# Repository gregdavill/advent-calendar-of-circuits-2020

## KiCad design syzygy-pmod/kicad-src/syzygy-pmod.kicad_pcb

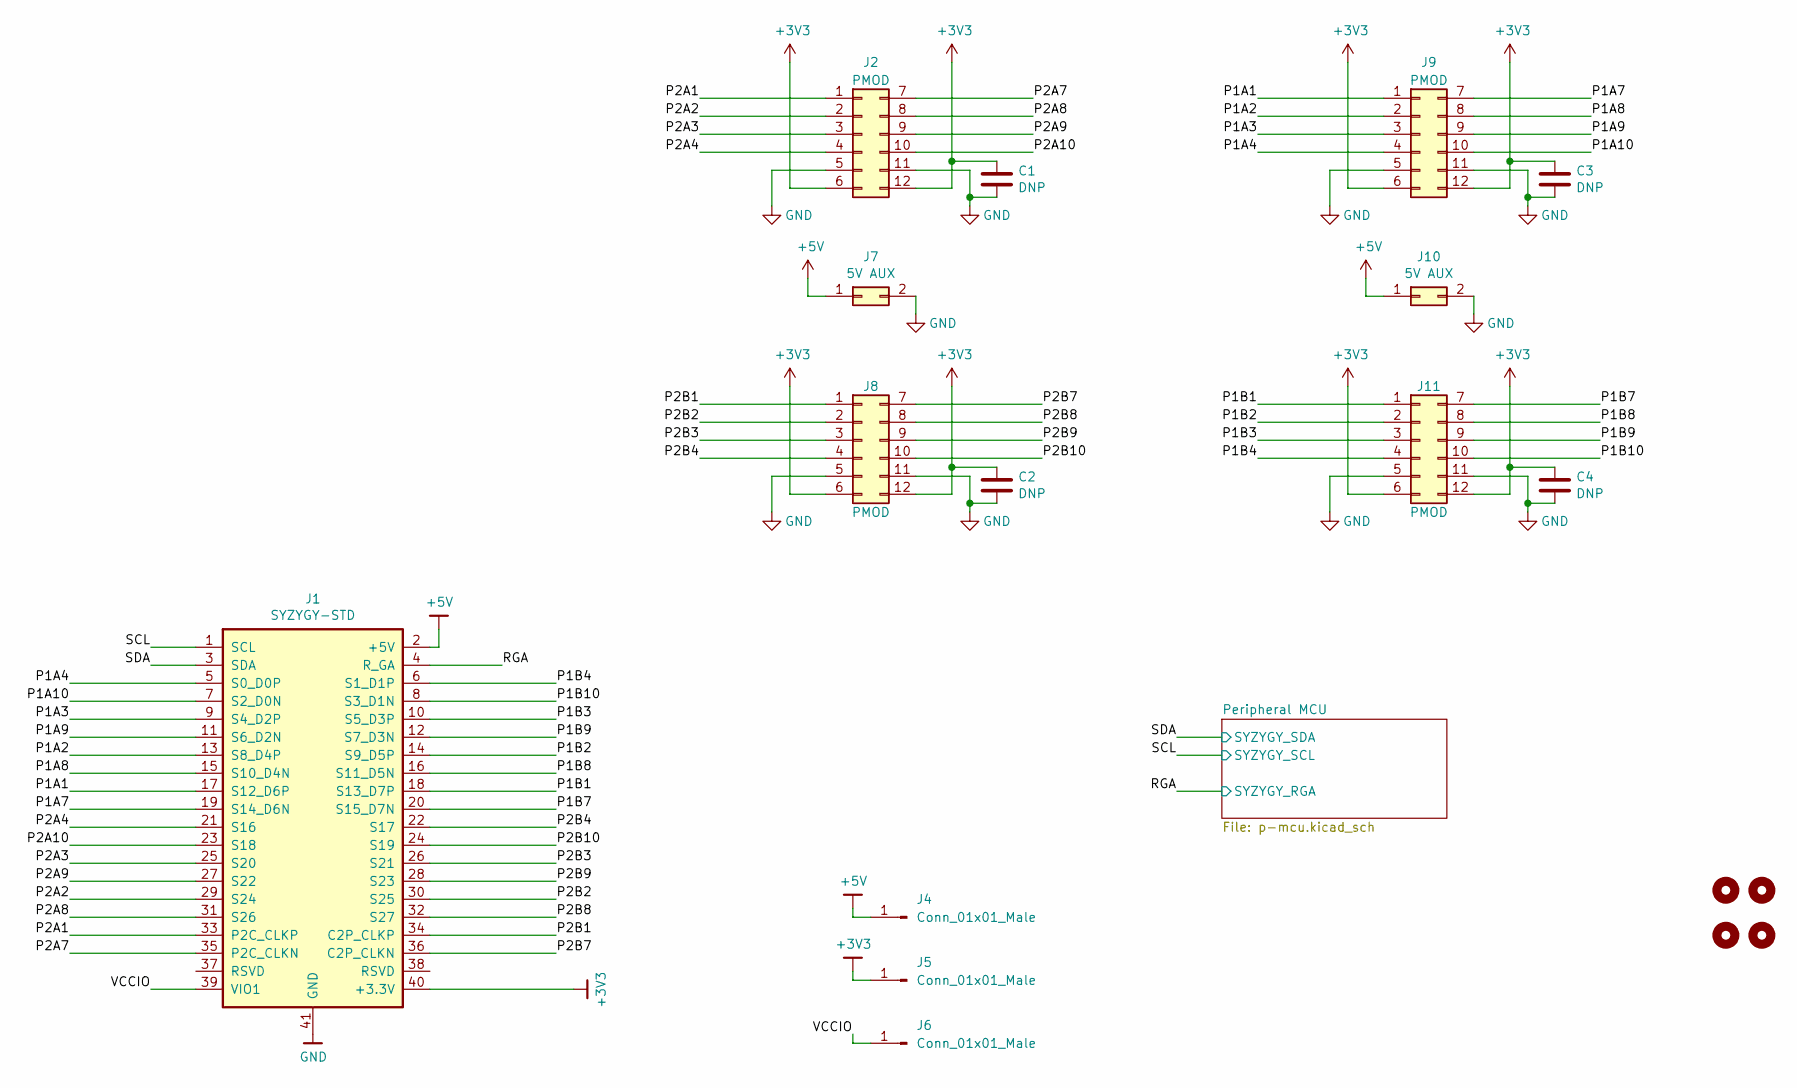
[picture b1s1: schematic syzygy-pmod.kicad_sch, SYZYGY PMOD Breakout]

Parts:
C1, C2, C3, C4: DNP; C_0603_1608Metric
H1, H2, H3, H4: MountingHole; MountingHole_3.2mm_M3_DIN965
J1: SYZYGY-STD; SYZYGY-STD-POD
J2, J8, J9, J11: PMOD; PMOD_Angled_2x06
J4, J5, J6: Conn_01x01_Male; PinHeader_1x01_P2.54mm_Vertical
J7, J10: 5V AUX; PinHeader_2x01_P2.54mm_Vertical

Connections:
+3V3: C1.2, C2.2, C3.2, C4.2, J1.40 (+3.3V), J2.6, J2.12, J5.1, J8.6, J8.12, J9.6, J9.12, J11.6, J11.12; also elsewhere on the board
+5V: J1.2 (+5V), J4.1, J7.1, J10.1
/P1A1: J1.17 (S12_D6P), J9.1
/P1A2: J1.13 (S8_D4P), J9.2
/P1A3: J1.9 (S4_D2P), J9.3
/P1A4: J1.5 (S0_D0P), J9.4
/P1A7: J1.19 (S14_D6N), J9.7
/P1A8: J1.15 (S10_D4N), J9.8
/P1A9: J1.11 (S6_D2N), J9.9
/P1A10: J1.7 (S2_D0N), J9.10
/P1B1: J1.18 (S13_D7P), J11.1
/P1B2: J1.14 (S9_D5P), J11.2
/P1B3: J1.10 (S5_D3P), J11.3
/P1B4: J1.6 (S1_D1P), J11.4
/P1B7: J1.20 (S15_D7N), J11.7
/P1B8: J1.16 (S11_D5N), J11.8
/P1B9: J1.12 (S7_D3N), J11.9
/P1B10: J1.8 (S3_D1N), J11.10
/P2A1: J1.33 (P2C_CLKP), J2.1
/P2A2: J1.29 (S24), J2.2
/P2A3: J1.25 (S20), J2.3
/P2A4: J1.21 (S16), J2.4
/P2A7: J1.35 (P2C_CLKN), J2.7
/P2A8: J1.31 (S26), J2.8
/P2A9: J1.27 (S22), J2.9
/P2A10: J1.23 (S18), J2.10
/P2B1: J1.34 (C2P_CLKP), J8.1
/P2B2: J1.30 (S25), J8.2
/P2B3: J1.26 (S21), J8.3
/P2B4: J1.22 (S17), J8.4
/P2B7: J1.36 (C2P_CLKN), J8.7
/P2B8: J1.32 (S27), J8.8
/P2B9: J1.28 (S23), J8.9
/P2B10: J1.24 (S19), J8.10
/RGA: J1.4 (R_GA); also elsewhere on the board
/SCL: J1.1 (SCL); also elsewhere on the board
/SDA: J1.3 (SDA); also elsewhere on the board
/VCCIO: J1.39 (VIO1), J6.1
GND: C1.1, C2.1, C3.1, C4.1, J1.41 (GND), J2.5, J2.11, J7.2, J8.5, J8.11, J9.5, J9.11, J10.2, J11.5, J11.11; also elsewhere on the board

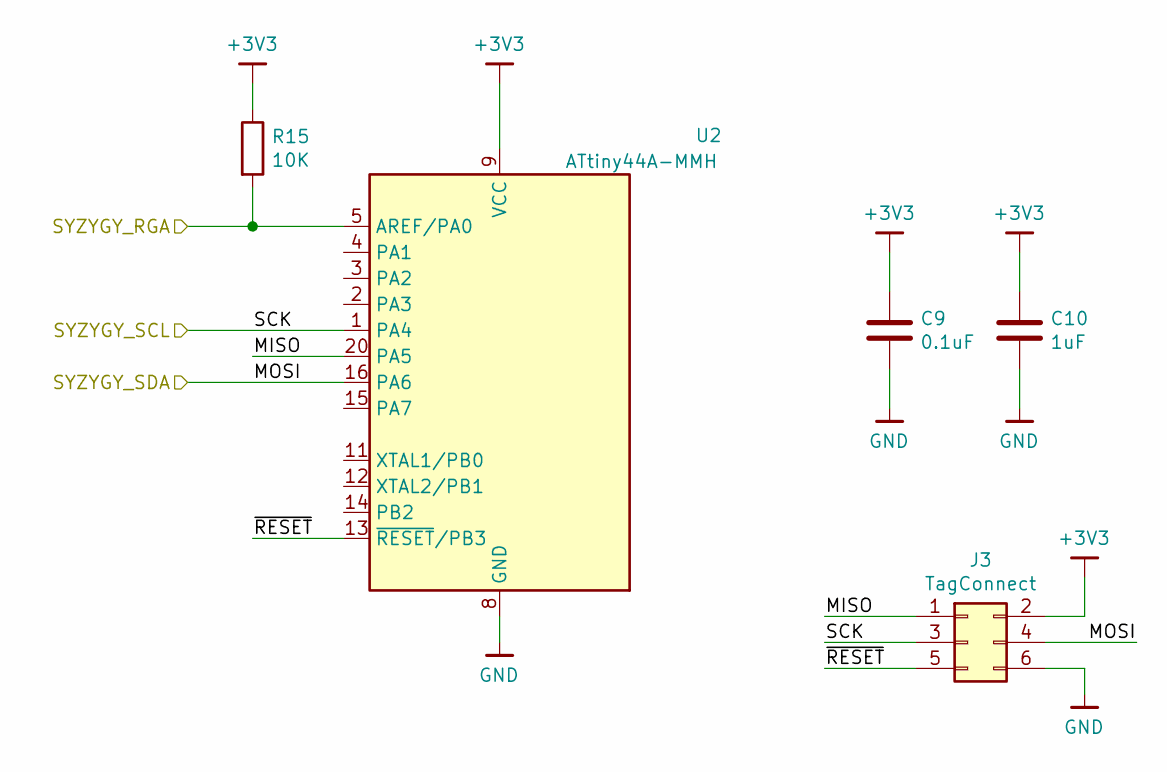
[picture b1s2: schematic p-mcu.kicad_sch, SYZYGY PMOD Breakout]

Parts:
C9: 0.1uF; C_0402_1005Metric
C10: 1uF; C_0402_1005Metric
J3: TagConnect; TC2030-NL_SMALL
R15: 10K; R_0402_1005Metric
U2: ATtiny44A-MMH; QFN-20-1EP_3x3mm_P0.45mm_EP1.6x1.6mm

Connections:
+3V3: C9.1, C10.1, J3.2, R15.1, U2.9 (VCC); also elsewhere on the board
/Peripheral MCU/MISO: J3.1, U2.20 (PA5)
/Peripheral MCU/~RESET: J3.5, U2.13 (~RESET~/PB3)
/RGA: R15.2, U2.5 (AREF/PA0); also elsewhere on the board
/SCL: J3.3, U2.1 (PA4); also elsewhere on the board
/SDA: J3.4, U2.16 (PA6); also elsewhere on the board
GND: C9.2, C10.2, J3.6, U2.8 (GND), U2.21 (GND); also elsewhere on the board
no_connect_51: U2.10 (NC)
no_connect_52: U2.17 (NC)
no_connect_53: U2.18 (NC)
no_connect_54: U2.19 (NC)
no_connect_55: U2.6 (NC)
no_connect_56: U2.7 (NC)

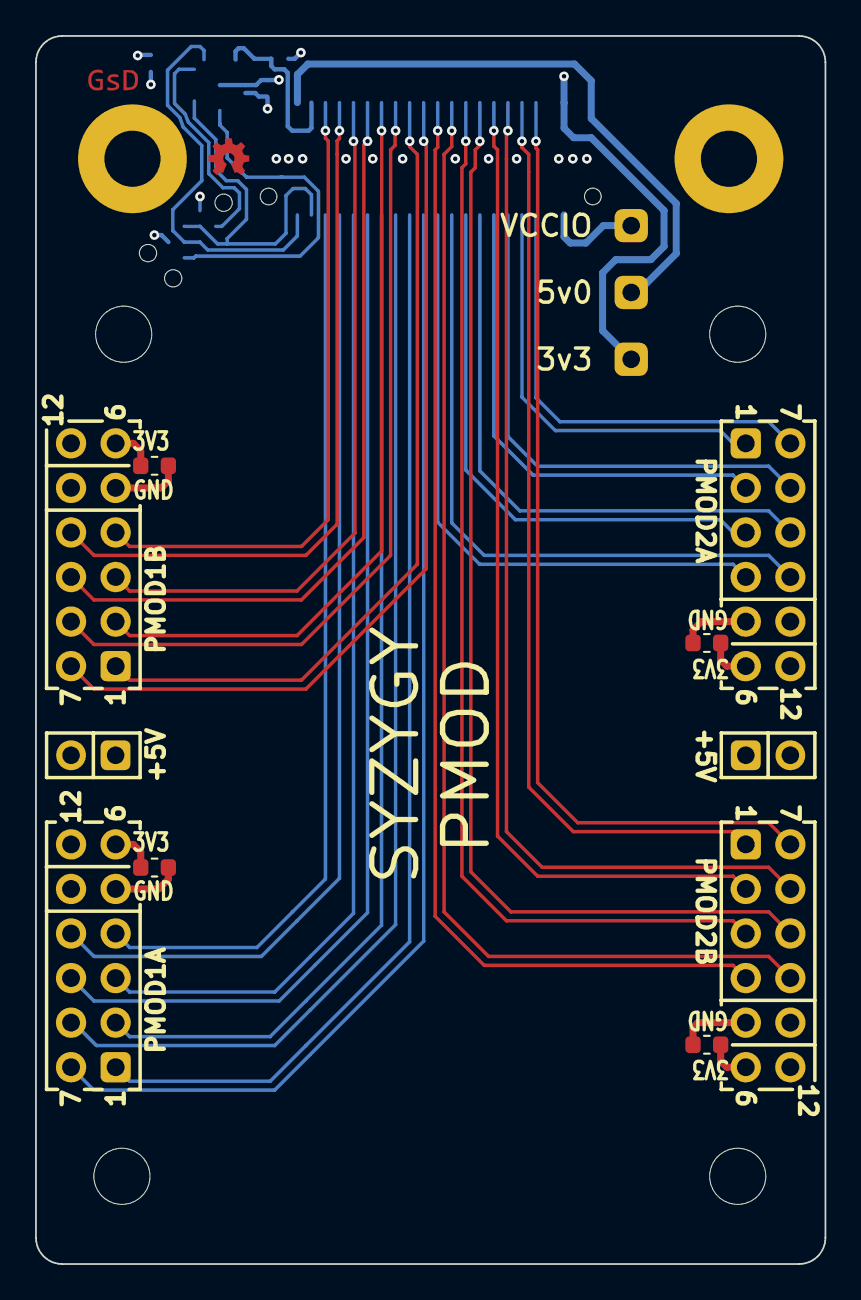
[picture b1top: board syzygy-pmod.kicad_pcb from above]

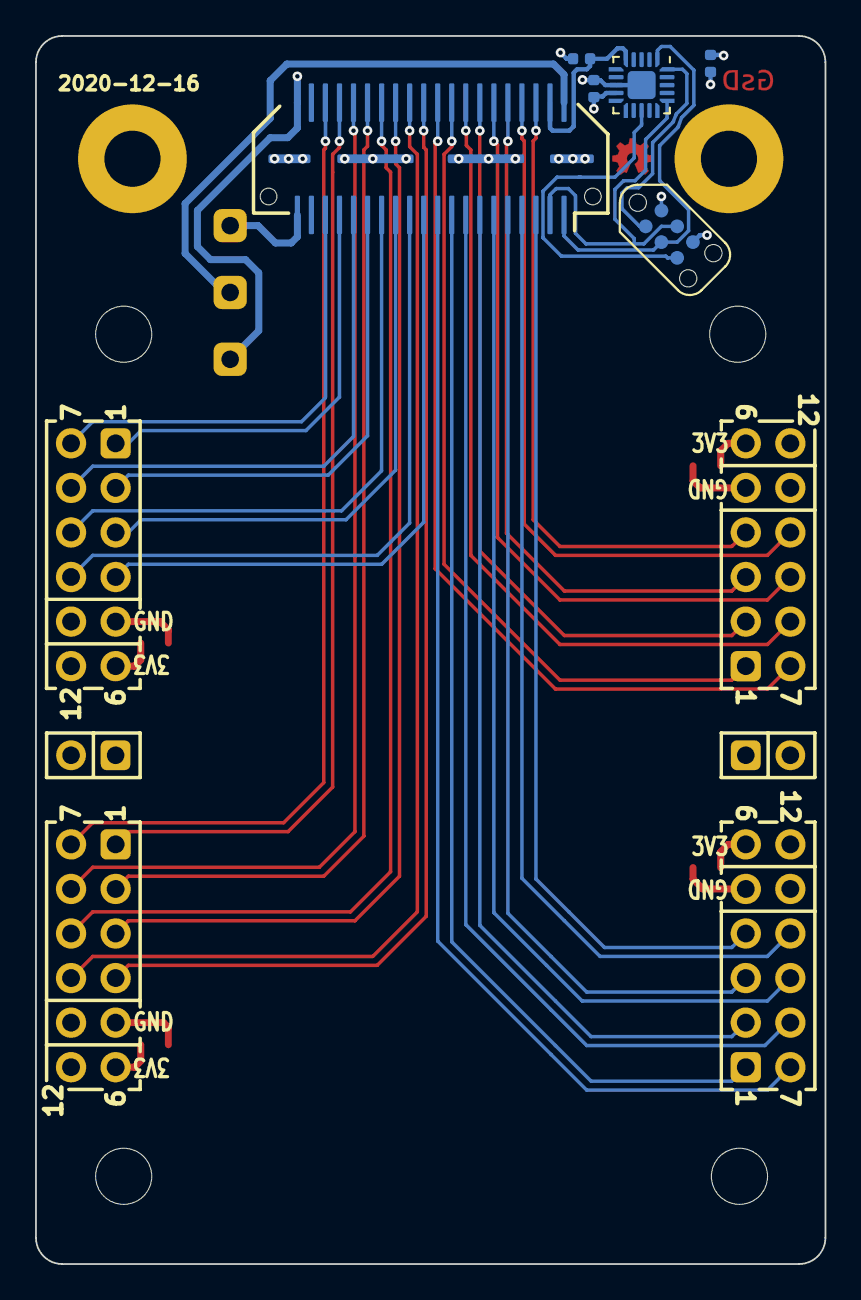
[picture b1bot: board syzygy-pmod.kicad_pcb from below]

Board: 4 copper layers, 45.0 x 70.0 mm, 23 parts (6 on the bottom side), 41 nets.

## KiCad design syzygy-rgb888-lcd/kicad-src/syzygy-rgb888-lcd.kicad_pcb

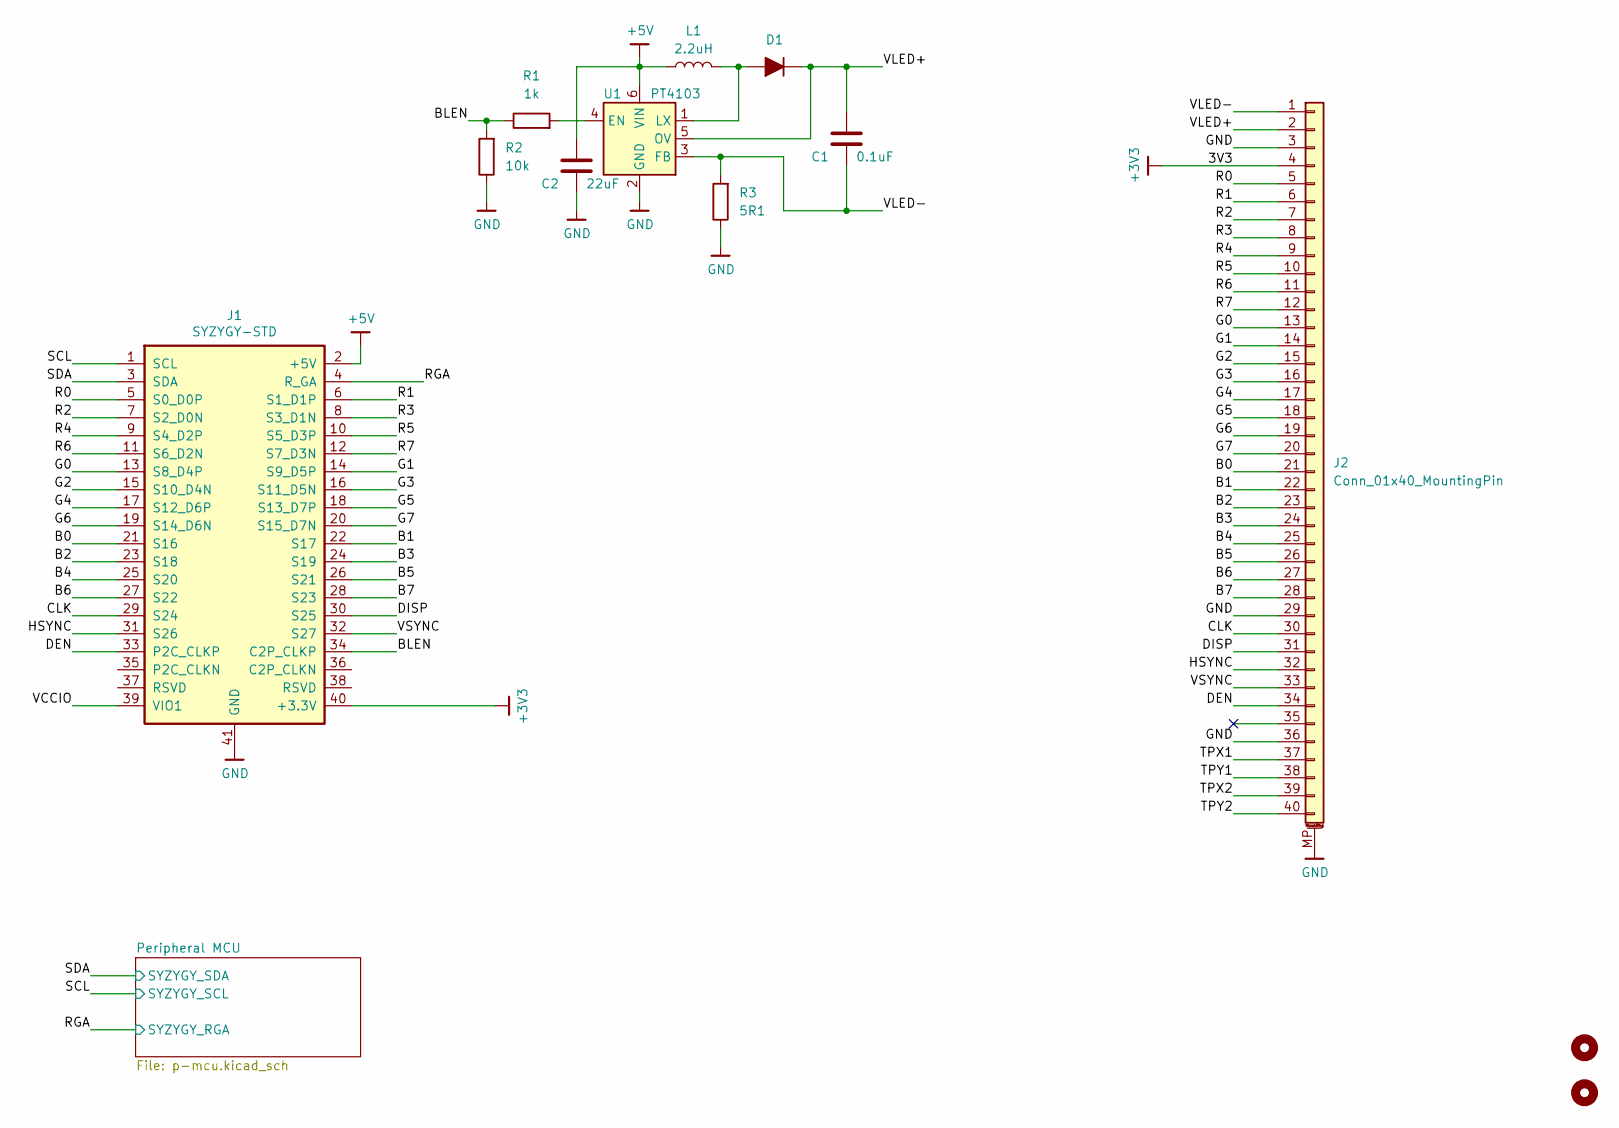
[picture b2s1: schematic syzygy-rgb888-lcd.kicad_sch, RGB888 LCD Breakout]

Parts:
C1: 0.1uF; C_0603_1608Metric
C2: 22uF; C_0603_1608Metric
D1: D_ALT; D_SOD-123F
H1, H2: MountingHole; MountingHole_3.2mm_M3_DIN965
J1: SYZYGY-STD; SYZYGY-STD-POD
J2: Conn_01x40_MountingPin; X05A20H40G
L1: 2.2uH; L_Taiyo-Yuden_MD-2020
R1: 1k; R_0402_1005Metric
R2: 10k; R_0402_1005Metric
R3: 5R1; R_0402_1005Metric
U1: PT4103; SOT-23-6

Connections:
+3V3: J1.40 (+3.3V), J2.4; also elsewhere on the board
+5V: C2.1, J1.2 (+5V), L1.1, U1.6 (VIN)
/B0: J1.21 (S16), J2.21
/B1: J1.22 (S17), J2.22
/B2: J1.23 (S18), J2.23
/B3: J1.24 (S19), J2.24
/B4: J1.25 (S20), J2.25
/B5: J1.26 (S21), J2.26
/B6: J1.27 (S22), J2.27
/B7: J1.28 (S23), J2.28
/BLEN: J1.34 (C2P_CLKP), R1.1, R2.2
/CLK: J1.29 (S24), J2.30
/DEN: J1.33 (P2C_CLKP), J2.34
/DISP: J1.30 (S25), J2.31
/G0: J1.13 (S8_D4P), J2.13
/G1: J1.14 (S9_D5P), J2.14
/G2: J1.15 (S10_D4N), J2.15
/G3: J1.16 (S11_D5N), J2.16
/G4: J1.17 (S12_D6P), J2.17
/G5: J1.18 (S13_D7P), J2.18
/G6: J1.19 (S14_D6N), J2.19
/G7: J1.20 (S15_D7N), J2.20
/HSYNC: J1.31 (S26), J2.32
/R0: J1.5 (S0_D0P), J2.5
/R1: J1.6 (S1_D1P), J2.6
/R2: J1.7 (S2_D0N), J2.7
/R3: J1.8 (S3_D1N), J2.8
/R4: J1.9 (S4_D2P), J2.9
/R5: J1.10 (S5_D3P), J2.10
/R6: J1.11 (S6_D2N), J2.11
/R7: J1.12 (S7_D3N), J2.12
/RGA: J1.4 (R_GA); also elsewhere on the board
/SCL: J1.1 (SCL); also elsewhere on the board
/SDA: J1.3 (SDA); also elsewhere on the board
/TPX1: J2.37
/TPX2: J2.39
/TPY1: J2.38
/TPY2: J2.40
/VCCIO: J1.39 (VIO1)
/VLED+: C1.1, D1.1 (K), J2.2, U1.5 (OV)
/VLED-: C1.2, J2.1, R3.2, U1.3 (FB)
/VSYNC: J1.32 (S27), J2.33
GND: C2.2, J1.41 (GND), J2.3, J2.29, J2.36, J2.MP (MountPin), R2.1, R3.1, U1.2 (GND); also elsewhere on the board
unnamed: D1.2 (A), L1.2, U1.1 (LX)
unnamed: R1.2, U1.4 (EN)
no_connect_59: J2.35

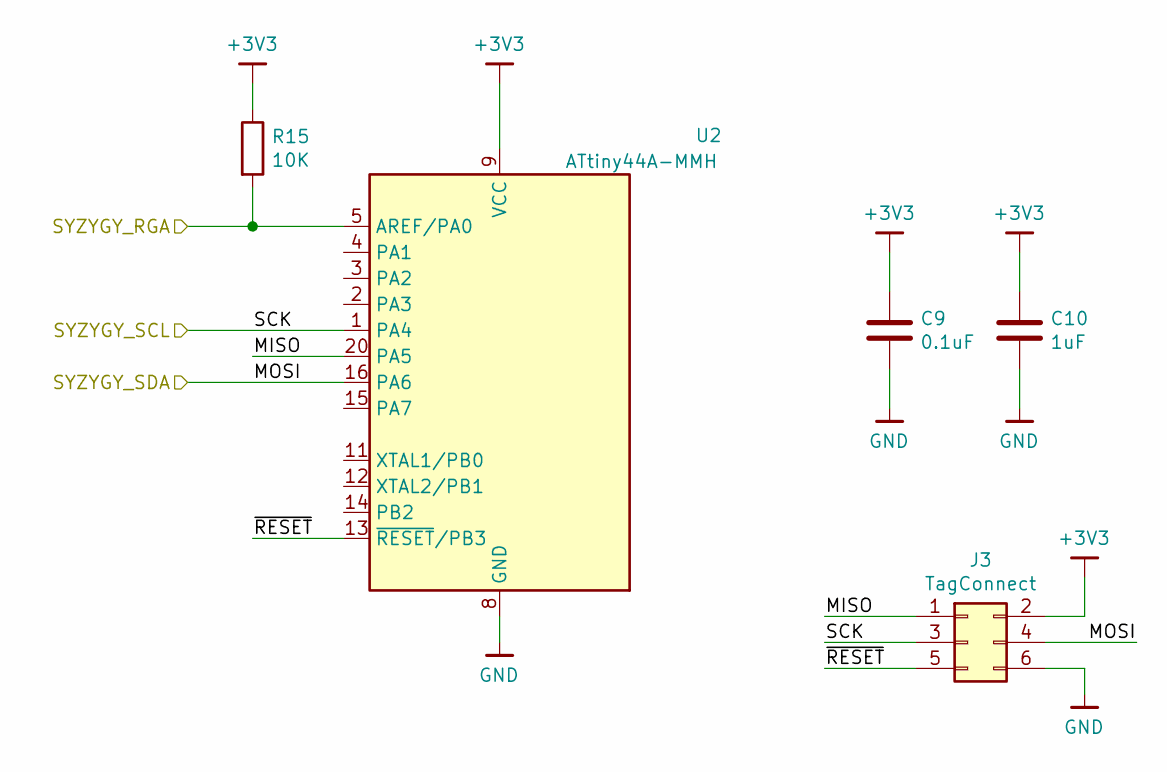
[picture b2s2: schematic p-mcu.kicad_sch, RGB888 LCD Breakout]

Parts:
C9: 0.1uF; C_0402_1005Metric
C10: 1uF; C_0402_1005Metric
J3: TagConnect; TC2030-NL_SMALL
R15: 10K; R_0402_1005Metric
U2: ATtiny44A-MMH; QFN-20-1EP_3x3mm_P0.45mm_EP1.6x1.6mm

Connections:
+3V3: C9.1, C10.1, J3.2, R15.1, U2.9 (VCC); also elsewhere on the board
/Peripheral MCU/MISO: J3.1, U2.20 (PA5)
/Peripheral MCU/~RESET: J3.5, U2.13 (~RESET~/PB3)
/RGA: R15.2, U2.5 (AREF/PA0); also elsewhere on the board
/SCL: J3.3, U2.1 (PA4); also elsewhere on the board
/SDA: J3.4, U2.16 (PA6); also elsewhere on the board
GND: C9.2, C10.2, J3.6, U2.8 (GND), U2.21 (GND); also elsewhere on the board
no_connect_60: U2.10 (NC)
no_connect_61: U2.17 (NC)
no_connect_62: U2.18 (NC)
no_connect_63: U2.19 (NC)
no_connect_64: U2.6 (NC)
no_connect_65: U2.7 (NC)

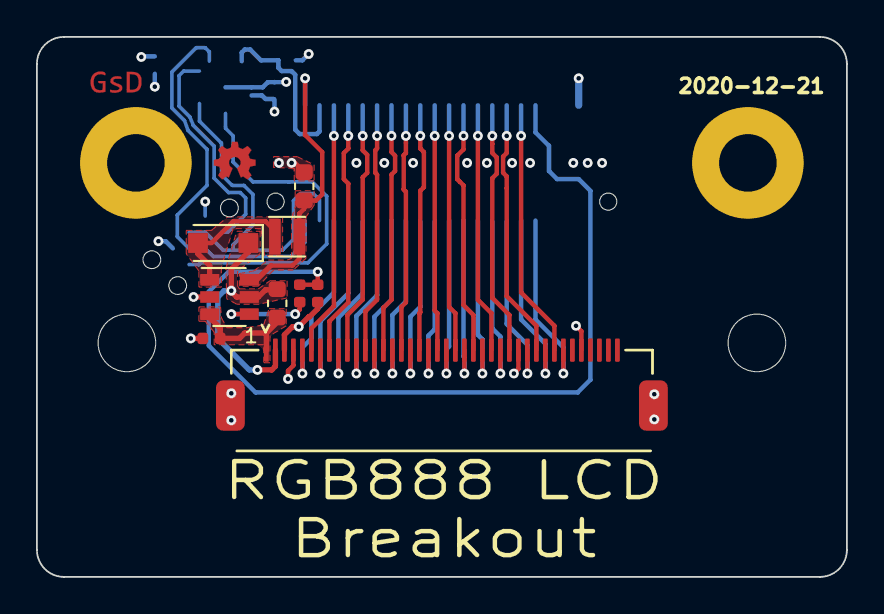
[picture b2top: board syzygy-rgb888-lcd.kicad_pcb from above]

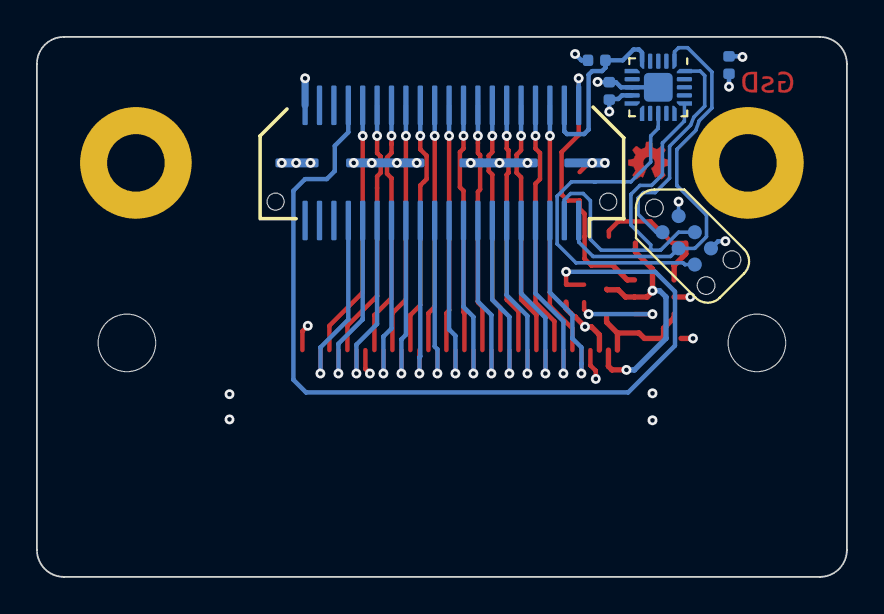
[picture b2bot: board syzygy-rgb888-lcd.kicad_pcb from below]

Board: 4 copper layers, 45.0 x 30.0 mm, 17 parts (6 on the bottom side), 42 nets.

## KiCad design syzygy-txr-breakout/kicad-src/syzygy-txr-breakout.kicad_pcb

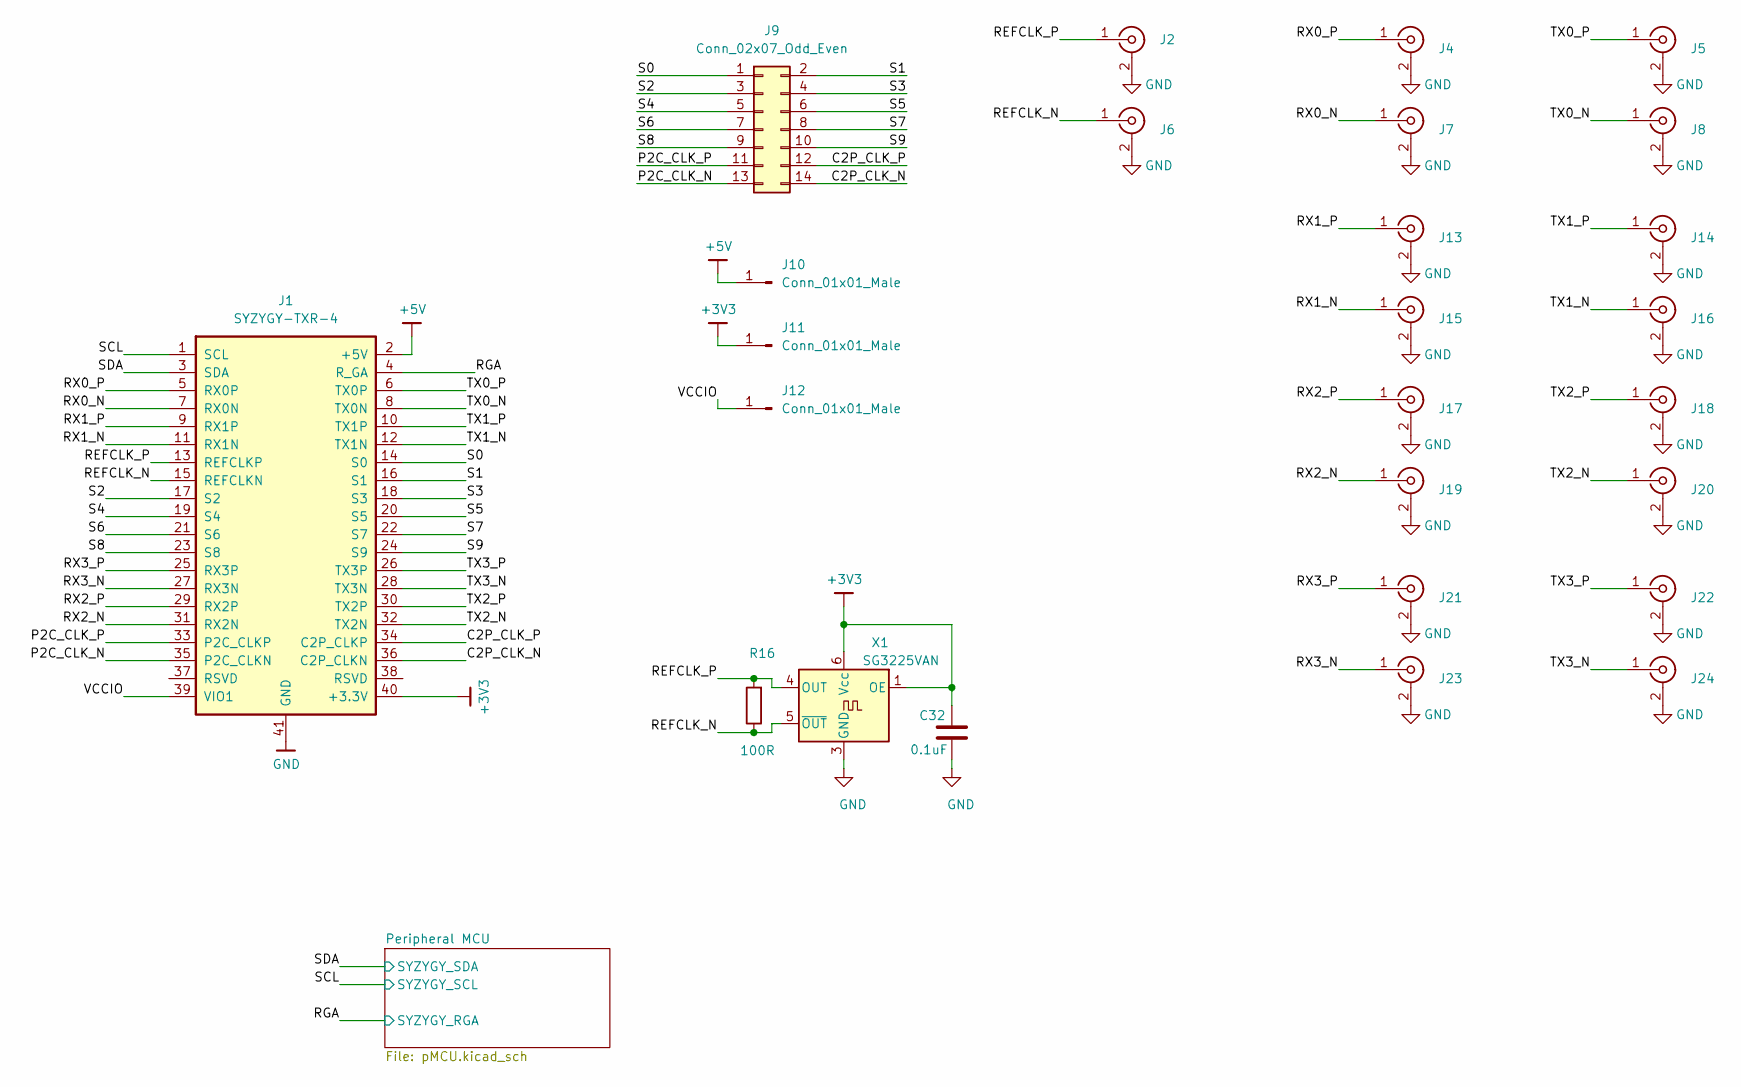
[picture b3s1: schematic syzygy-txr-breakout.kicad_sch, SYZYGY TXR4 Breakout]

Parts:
C32: 0.1uF; C_0402_1005Metric
J1: SYZYGY-TXR-4; SYZYGY-TXR-POD
J2, J4, J5, J6, J7, J8, J13, J14, J15, J16, J17, J18, J19, J20, J21, J22, J23, J24: sma jack; SMA_Amphenol_132134_Vertical
J9: Conn_02x07_Odd_Even; PinHeader_2x07_P2.54mm_Vertical
J10, J11, J12: Conn_01x01_Male; PinHeader_1x01_P2.54mm_Vertical
R16: 100R; R_0402_1005Metric
X1: SG3225VAN; Oscillator_SMD_Silicon_Labs_LGA-6_2.5x3.2mm_P1.25mm

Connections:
+3V3: C32.1, J1.40 (+3.3V), J11.1, X1.1 (OE), X1.6 (Vcc); also elsewhere on the board
+5V: J1.2 (+5V), J10.1
/C2P_CLK_N: J1.36 (C2P_CLKN), J9.14
/C2P_CLK_P: J1.34 (C2P_CLKP), J9.12
/P2C_CLK_N: J1.35 (P2C_CLKN), J9.13
/P2C_CLK_P: J1.33 (P2C_CLKP), J9.11
/REFCLK_N: J1.15 (REFCLKN), J6.1 (In), R16.1, X1.5 (~OUT)
/REFCLK_P: J1.13 (REFCLKP), J2.1 (In), R16.2, X1.4 (OUT)
/RGA: J1.4 (R_GA); also elsewhere on the board
/RX0_N: J1.7 (RX0N), J7.1 (In)
/RX0_P: J1.5 (RX0P), J4.1 (In)
/RX1_N: J1.11 (RX1N), J15.1 (In)
/RX1_P: J1.9 (RX1P), J13.1 (In)
/RX2_N: J1.31 (RX2N), J19.1 (In)
/RX2_P: J1.29 (RX2P), J17.1 (In)
/RX3_N: J1.27 (RX3N), J23.1 (In)
/RX3_P: J1.25 (RX3P), J21.1 (In)
/S0: J1.14 (S0), J9.1
/S1: J1.16 (S1), J9.2
/S2: J1.17 (S2), J9.3
/S3: J1.18 (S3), J9.4
/S4: J1.19 (S4), J9.5
/S5: J1.20 (S5), J9.6
/S6: J1.21 (S6), J9.7
/S7: J1.22 (S7), J9.8
/S8: J1.23 (S8), J9.9
/S9: J1.24 (S9), J9.10
/SCL: J1.1 (SCL); also elsewhere on the board
/SDA: J1.3 (SDA); also elsewhere on the board
/TX0_N: J1.8 (TX0N), J8.1 (In)
/TX0_P: J1.6 (TX0P), J5.1 (In)
/TX1_N: J1.12 (TX1N), J16.1 (In)
/TX1_P: J1.10 (TX1P), J14.1 (In)
/TX2_N: J1.32 (TX2N), J20.1 (In)
/TX2_P: J1.30 (TX2P), J18.1 (In)
/TX3_N: J1.28 (TX3N), J24.1 (In)
/TX3_P: J1.26 (TX3P), J22.1 (In)
/VCCIO: J1.39 (VIO1), J12.1
GND: C32.2, J1.41 (GND), J2.2 (Ext), J4.2 (Ext), J5.2 (Ext), J6.2 (Ext), J7.2 (Ext), J8.2 (Ext), J13.2 (Ext), J14.2 (Ext), J15.2 (Ext), J16.2 (Ext), J17.2 (Ext), J18.2 (Ext), J19.2 (Ext), J20.2 (Ext), J21.2 (Ext), J22.2 (Ext), J23.2 (Ext), J24.2 (Ext), X1.3 (GND); also elsewhere on the board

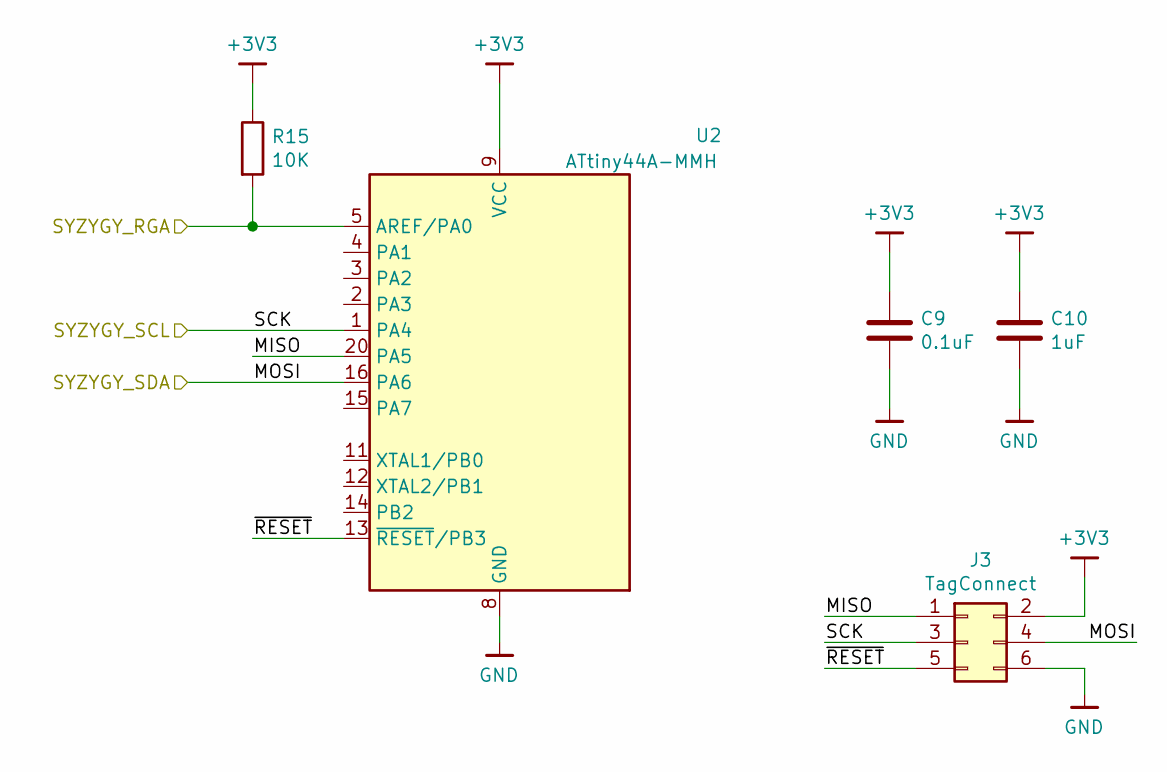
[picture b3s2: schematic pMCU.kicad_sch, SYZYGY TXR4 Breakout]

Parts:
C9: 0.1uF; C_0402_1005Metric
C10: 1uF; C_0402_1005Metric
J3: TagConnect; TC2030-NL_SMALL
R15: 10K; R_0402_1005Metric
U2: ATtiny44A-MMH; QFN-20-1EP_3x3mm_P0.45mm_EP1.6x1.6mm

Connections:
+3V3: C9.1, C10.1, J3.2, R15.1, U2.9 (VCC); also elsewhere on the board
/Peripheral MCU/MISO: J3.1, U2.20 (PA5)
/Peripheral MCU/~RESET: J3.5, U2.13 (~RESET~/PB3)
/RGA: R15.2, U2.5 (AREF/PA0); also elsewhere on the board
/SCL: J3.3, U2.1 (PA4); also elsewhere on the board
/SDA: J3.4, U2.16 (PA6); also elsewhere on the board
GND: C9.2, C10.2, J3.6, U2.8 (GND), U2.21 (GND); also elsewhere on the board
no_connect_51: U2.10 (NC)
no_connect_52: U2.17 (NC)
no_connect_53: U2.18 (NC)
no_connect_54: U2.19 (NC)
no_connect_55: U2.6 (NC)
no_connect_56: U2.7 (NC)

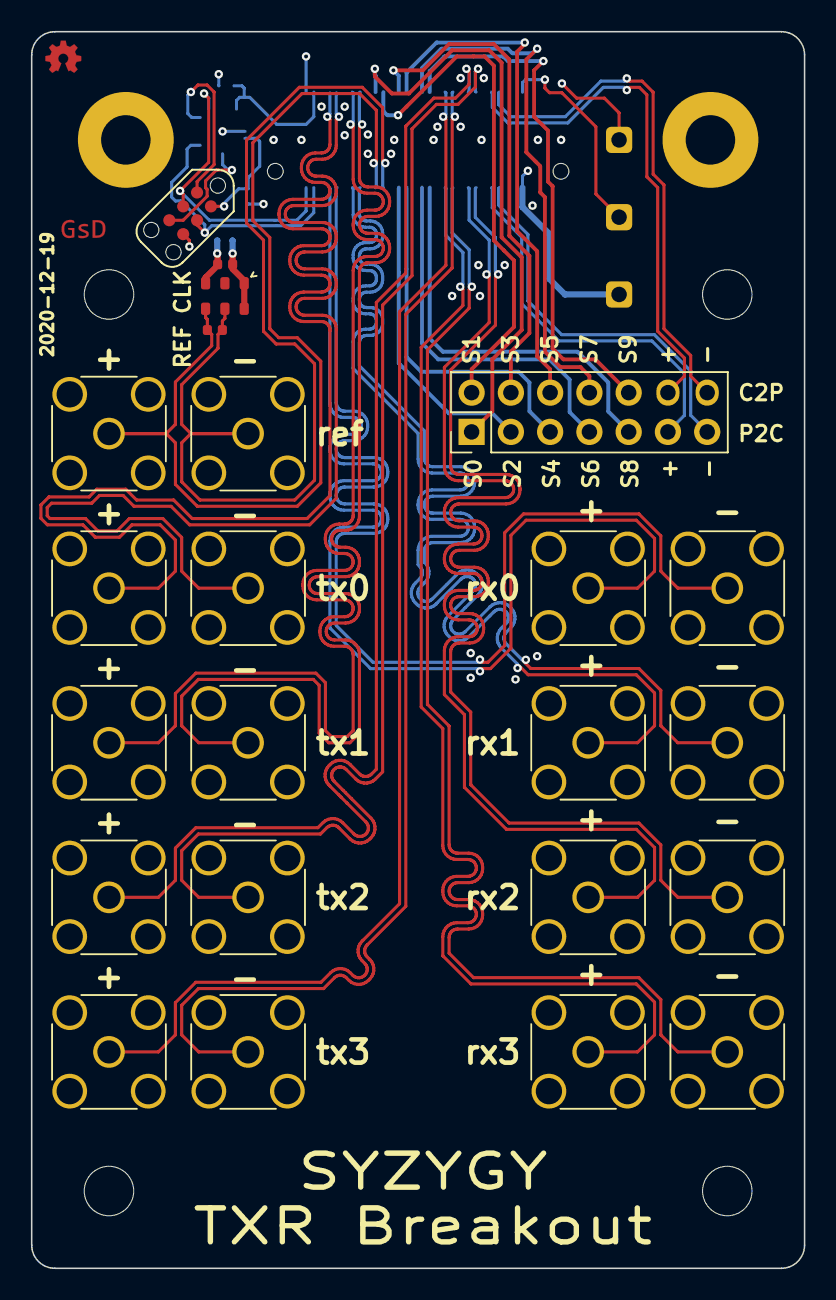
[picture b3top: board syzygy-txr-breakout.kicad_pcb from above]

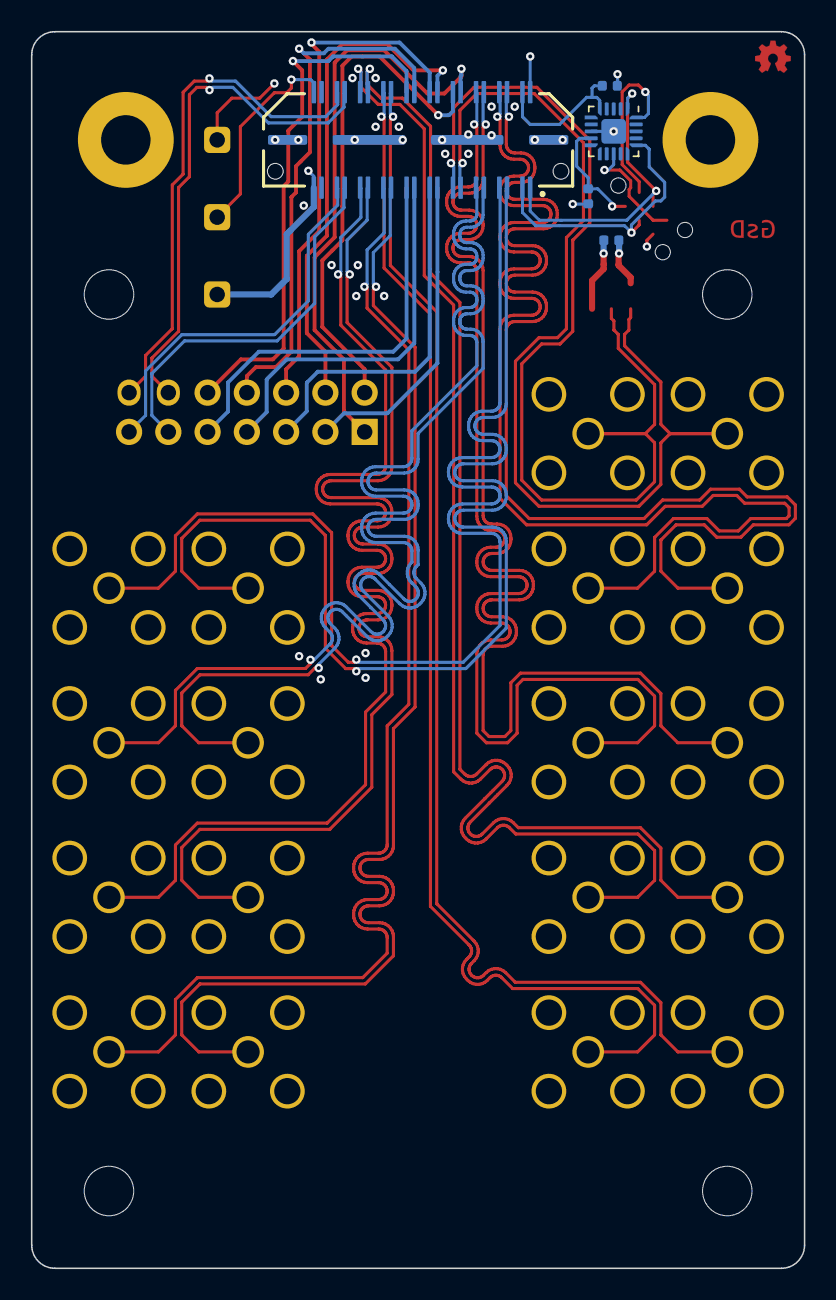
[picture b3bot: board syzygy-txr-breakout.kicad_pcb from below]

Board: 4 copper layers, 50.0 x 80.0 mm, 35 parts (5 on the bottom side), 41 nets.

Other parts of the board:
H1, H2, H3, H4: MountingHole; MountingHole_3.2mm_M3
